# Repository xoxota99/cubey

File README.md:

# Cubey - Rubik's Cube Solving Robot

Cubey is a Raspberry Pi-based Rubik's Cube solving robot that uses computer vision to scan a cube, calculates a solution, and manipulates the cube to solve it using stepper motors.

## Features

- Computer vision-based cube scanning with OpenCV
- Efficient solving algorithm using Kociemba's two-phase algorithm
- Precise stepper motor control for cube manipulation
- Web interface for remote operation
- Command-line interface for local operation
- Comprehensive logging and error handling
- Performance optimizations for faster solving

## Project Structure

```
/
├── config/                     # Configuration files
│   ├── config.yaml             # Main configuration
│   └── calibration.yaml        # Camera calibration
│
├── cubey/                      # Main package directory
│   ├── __init__.py             # Package initialization with version
│   ├── cli.py                  # Command-line interface
│   ├── exceptions.py           # Custom exceptions
│   │
│   ├── config/                 # Configuration management
│   │   ├── __init__.py
│   │   ├── defaults.py         # Default configuration values
│   │   ├── loader.py           # Configuration loading
│   │   ├── schema.py           # Configuration schema
│   │   └── validation.py       # Configuration validation
│   │
│   ├── hardware/               # Hardware interfaces
│   │   ├── __init__.py
│   │   ├── camera.py           # Camera interface
│   │   ├── motorcontroller.py  # Motor controller
│   │   ├── motors.py           # Interactive motor control
│   │   └── calibration.py      # Hardware calibration
│   │
│   ├── solver/                 # Cube solving algorithms
│   │   ├── __init__.py
│   │   ├── kociemba_solver.py  # Kociemba solver
│   │   ├── scanner.py          # Cube state scanner
│   │   └── scrambler.py        # Cube scrambler
│   │
│   ├── ui/                     # User interfaces
│   │   ├── __init__.py
│   │   ├── cli_controller.py   # CLI controller
│   │   └── web_controller.py   # Web interface controller
│   │
│   ├── utils/                  # Utility modules
│   │   ├── __init__.py
│   │   ├── error_handler.py    # Error handling
│   │   ├── logger.py           # Logging setup
│   │   └── logging_config.py   # Logging configuration
│   │
│   └── web/                    # Web interface
│       ├── __init__.py
│       ├── app.py              # Flask application
│       ├── camera.py           # Camera streaming
│       ├── frame_event.py      # Frame event handling
│       ├── integration.py      # API integration
│       ├── security.py         # Security utilities
│       └── webstream.py        # Video streaming
│
├── docs/                       # Documentation
│   ├── api.md                  # API documentation
│   ├── configuration.md        # Configuration guide
│   └── development.md          # Development guide
│
├── scripts/                    # Utility scripts
│   ├── install_dependencies.sh # Install system dependencies
│   └── profile_solver.py       # Solver profiling script
│
├── tests/                      # Test suite
│   ├── __init__.py
│   ├── conftest.py             # Test configuration
│   ├── test_solver.py          # Solver tests
│   └── test_scanner.py         # Scanner tests
│
├── setup.py                    # Package setup
├── pyproject.toml              # Project metadata
├── CONTRIBUTING.md             # Contribution guidelines
├── CHANGELOG.md                # Project changelog
└── README.md                   # This file
```

## Installation

### System Requirements

- Raspberry Pi 3 or newer
- Raspberry Pi Camera Module
- Stepper motors and drivers
- Python 3.10 or newer

### Install System Dependencies

```bash
# Run the dependency installation script
sudo ./scripts/install_dependencies.sh
```

### Install Cubey

```bash
# Create and activate a virtual environment
python -m venv venv
source venv/bin/activate  # On Windows: venv\Scripts\activate

# Install from PyPI
pip install cubey

# Or install from source
pip install -e .
```

## Quick Start

### Command Line Interface

```bash
# Solve a cube
cubey solve

# Scramble a cube
cubey scramble

# Calibrate the scanner
cubey calibrate

# Manual control of motors
cubey manual

# Start the web interface
cubey web
```

### Python API

```python
from cubey.hardware.motorcontroller import MotorController
from cubey.solver.scanner import Scanner
from cubey.solver.kociemba_solver import KociembaSolver
from cubey.config.loader import load_config

# Load configuration
config = load_config()

# Initialize components
scanner = Scanner(config)
motors = MotorController(config)
solver = KociembaSolver(config)

# Scan the cube
state = scanner.get_state_string(motors)

# Solve the cube
solution = solver.solve(state)
motors.execute(solution)
```

## Web Interface

Start the web server:

```bash
cubey web --host 0.0.0.0 --port 5000
```

Then open a browser to http://localhost:5000/

## Configuration

Configuration is stored in YAML files in the `config/` directory:

- `config/config.yaml`: Main configuration
- `config/calibration.yaml`: Camera calibration

You can override the configuration by creating a custom config file and specifying it with the `--config` option:

```bash
cubey --config /path/to/custom_config.yaml solve
```

All default configuration values are defined in `cubey/config/defaults.py`.

## Development

See [CONTRIBUTING.md](CONTRIBUTING.md) for development guidelines.

### Setting Up Development Environment

```bash
# Clone the repository
git clone https://github.com/cubey/cubey.git
cd cubey

# Create and activate a virtual environment
python -m venv venv
source venv/bin/activate  # On Windows: venv\Scripts\activate

# Install in development mode
pip install -e ".[dev]"
```

### Running Tests

```bash
pytest
```

## License

This project is licensed under the MIT License - see the [LICENSE](LICENSE) file for details.

## Acknowledgments

- [Herbert Kociemba](http://kociemba.org/cube.htm) for the two-phase algorithm
- [OpenCV](https://opencv.org/) for computer vision capabilities
- All contributors to this project

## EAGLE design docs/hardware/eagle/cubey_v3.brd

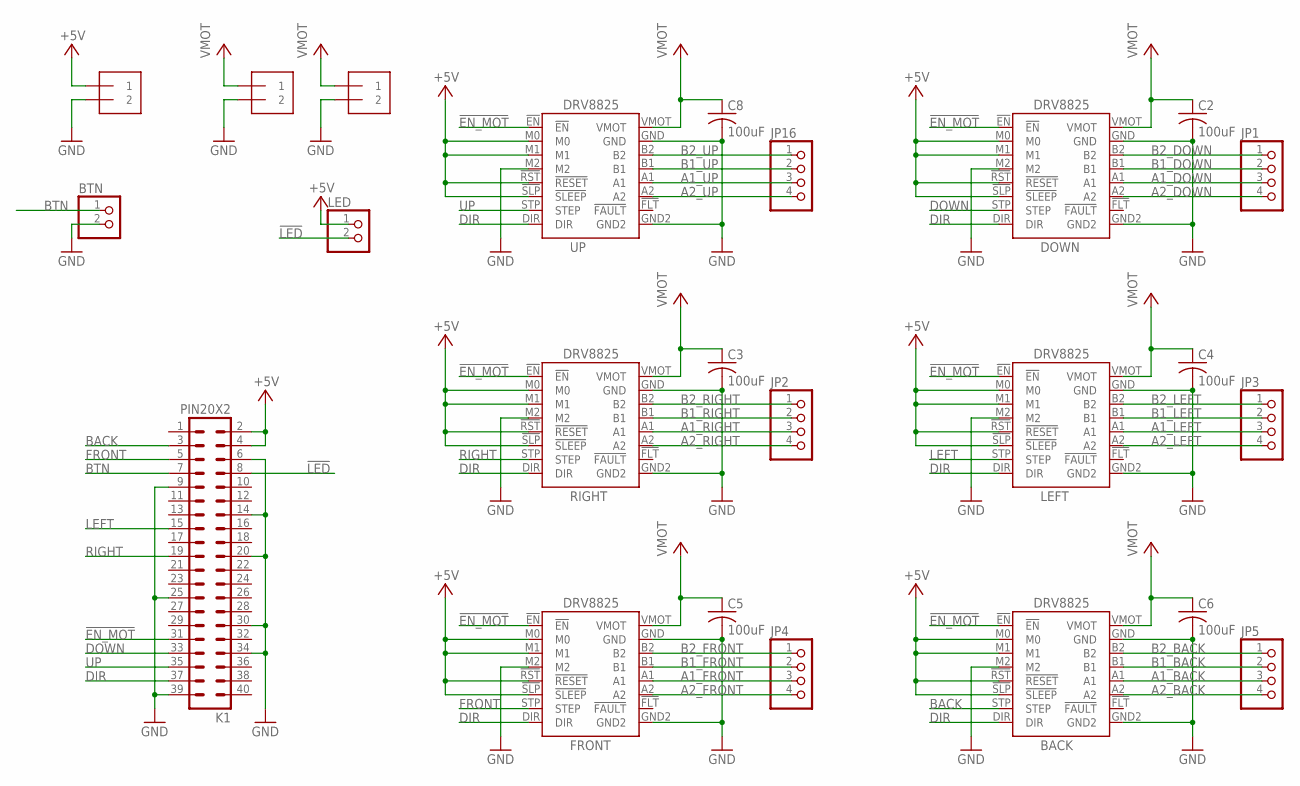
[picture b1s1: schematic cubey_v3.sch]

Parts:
5V_PWR: 1X2-3.5MM
BACK: DRV_8825_SOCKET; DRV_8825_DIP
BTN: PINHD-1X2; 1X02
C2, C3, C4, C5, C6, C8: 100uF; C025-025X050
DOWN: DRV_8825_SOCKET; DRV_8825_DIP
FRONT: DRV_8825_SOCKET; DRV_8825_DIP
JP1, JP2, JP3, JP4, JP5, JP16: PINHD-1X4; 1X04
K1: PIN20X2; PIN_20X2
LED: PINHD-1X2; 1X02
LEFT: DRV_8825_SOCKET; DRV_8825_DIP
MOT_PWR, MOT_PWR1: 1X2-3.5MM
RIGHT: DRV_8825_SOCKET; DRV_8825_DIP
UP: DRV_8825_SOCKET; DRV_8825_DIP

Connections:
!EN_MOT: BACK.!EN, DOWN.!EN, FRONT.!EN, K1.31, LEFT.!EN, RIGHT.!EN, UP.!EN
!LED: K1.8, LED.2
+5V: 5V_PWR.1, BACK.!RST (!RESET), BACK.!SLP (!SLEEP), BACK.M0, BACK.M1, DOWN.!RST (!RESET), DOWN.!SLP (!SLEEP), DOWN.M0, DOWN.M1, FRONT.!RST (!RESET), FRONT.!SLP (!SLEEP), FRONT.M0, FRONT.M1, K1.2, K1.4, LED.1, LEFT.!RST (!RESET), LEFT.!SLP (!SLEEP), LEFT.M0, LEFT.M1, RIGHT.!RST (!RESET), RIGHT.!SLP (!SLEEP), RIGHT.M0, RIGHT.M1, UP.!RST (!RESET), UP.!SLP (!SLEEP), UP.M0, UP.M1
A1_BACK: BACK.A1, JP5.3
A1_DOWN: DOWN.A1, JP1.3
A1_FRONT: FRONT.A1, JP4.3
A1_LEFT: JP3.3, LEFT.A1
A1_RIGHT: JP2.3, RIGHT.A1
A1_UP: JP16.3, UP.A1
A2_BACK: BACK.A2, JP5.4
A2_DOWN: DOWN.A2, JP1.4
A2_FRONT: FRONT.A2, JP4.4
A2_LEFT: JP3.4, LEFT.A2
A2_RIGHT: JP2.4, RIGHT.A2
A2_UP: JP16.4, UP.A2
B1_BACK: BACK.B1, JP5.2
B1_DOWN: DOWN.B1, JP1.2
B1_FRONT: FRONT.B1, JP4.2
B1_LEFT: JP3.2, LEFT.B1
B1_RIGHT: JP2.2, RIGHT.B1
B1_UP: JP16.2, UP.B1
B2_BACK: BACK.B2, JP5.1
B2_DOWN: DOWN.B2, JP1.1
B2_FRONT: FRONT.B2, JP4.1
B2_LEFT: JP3.1, LEFT.B2
B2_RIGHT: JP2.1, RIGHT.B2
B2_UP: JP16.1, UP.B2
BACK: BACK.STP (STEP), K1.3
BTN: BTN.1, K1.7
DIR: BACK.DIR, DOWN.DIR, FRONT.DIR, K1.37, LEFT.DIR, RIGHT.DIR, UP.DIR
DOWN: DOWN.STP (STEP), K1.33
FRONT: FRONT.STP (STEP), K1.5
GND: 5V_PWR.2, BACK.GND, BACK.GND2, BACK.M2, BTN.2, C2.2, C3.2, C4.2, C5.2, C6.2, C8.2, DOWN.GND, DOWN.GND2, DOWN.M2, FRONT.GND, FRONT.GND2, FRONT.M2, K1.6, K1.9, K1.14, K1.20, K1.25, K1.30, K1.34, K1.39, LEFT.GND, LEFT.GND2, LEFT.M2, MOT_PWR.2, MOT_PWR1.2, RIGHT.GND, RIGHT.GND2, RIGHT.M2, UP.GND, UP.GND2, UP.M2
LEFT: K1.15, LEFT.STP (STEP)
RIGHT: K1.19, RIGHT.STP (STEP)
UP: K1.35, UP.STP (STEP)
VCC: BACK.VMOT, C2.1, C3.1, C4.1, C5.1, C6.1, C8.1, DOWN.VMOT, FRONT.VMOT, LEFT.VMOT, MOT_PWR.1, MOT_PWR1.1, RIGHT.VMOT, UP.VMOT

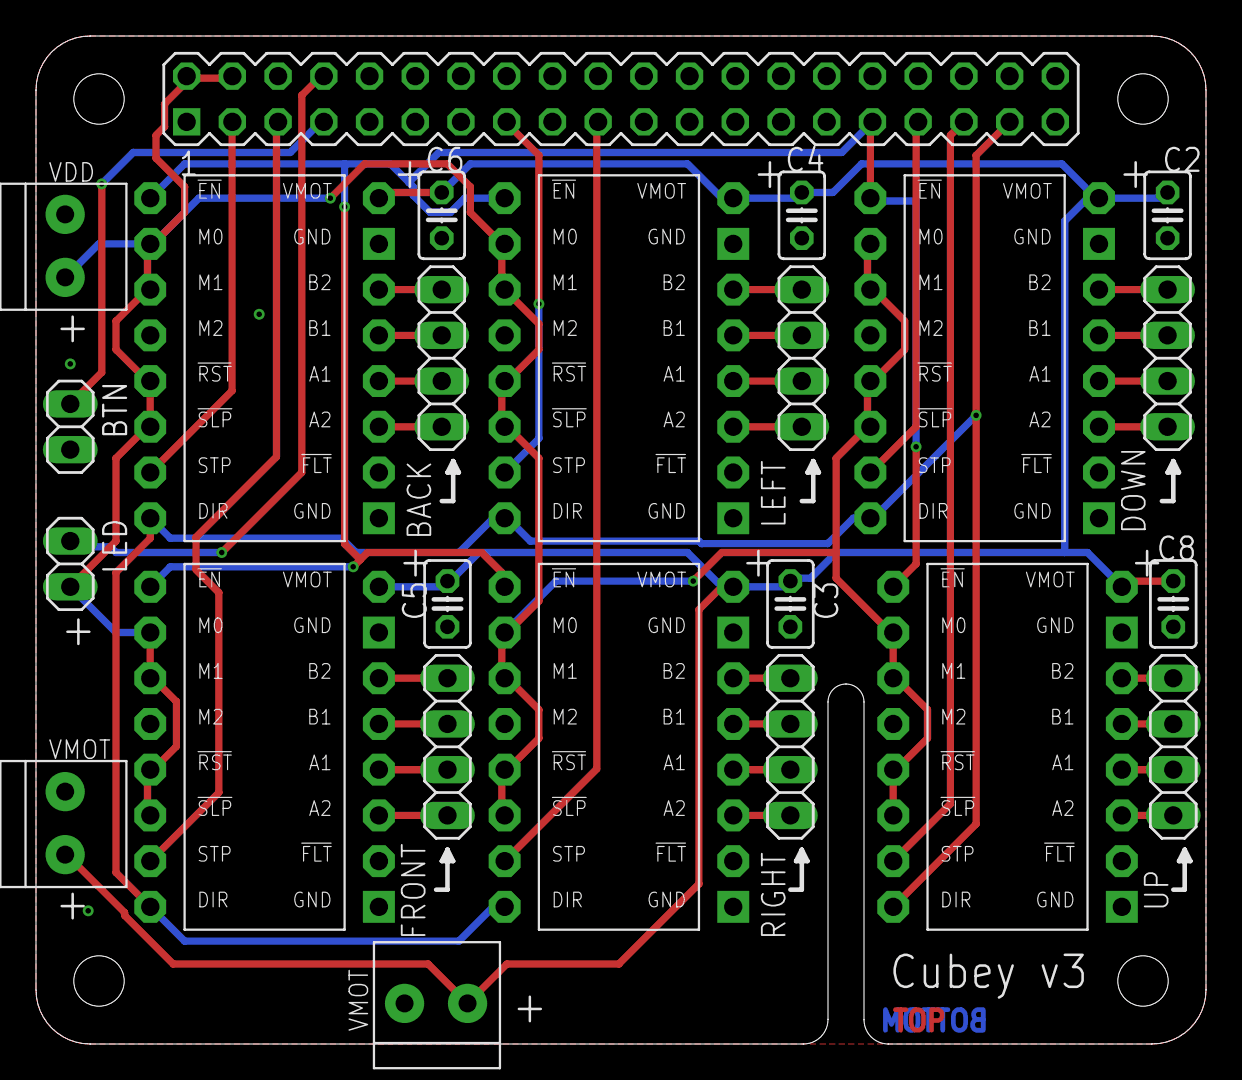
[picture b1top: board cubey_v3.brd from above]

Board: 2 copper layers, 65.0 x 56.0 mm, 24 parts (0 on the bottom side), 37 nets.

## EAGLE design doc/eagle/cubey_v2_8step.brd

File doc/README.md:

# Setting Up your Raspberry Pi
These instructions are for Ubuntu 21.04 or later on Raspberry Pi. Other than service setup, they should be applicable to any debian-based, reasonably recent OS (such as Raspbian, or whatever they're calling it now).

## The Basics
Install Ubuntu Server 21.04 or later: https://ubuntu.com/tutorials/how-to-install-ubuntu-on-your-raspberry-pi#1-overview 

SSH into your new, up-and-running RPi using "ubuntu/ubuntu". Change the password.

Create a new user (here we're creating a user "cubey"):

    sudo adduser cubey
    sudo adduser cubey sudo

(Optional) Enable passwordless login: https://linuxize.com/post/how-to-setup-passwordless-ssh-login/ 

SSH into your RPi as the new user you just created.

**Slow SSH logins?** Disable PAM auth: change `UsePAM` from `yes` to `no` in */etc/ssh/sshd_config*

    UsePAM no

(Optional) change the hostname in */etc/hostname*

(Optional) set the timezone: `sudo dpkg-reconfigure tzdata`

(Optional) install zsh: `sudo apt install zsh`

(Optional) set zsh as your default shell: `chsh -s $(which zsh)`

(Optional) install oh-my-zsh: `sh -c "$(curl -fsSL https://raw.github.com/ohmyzsh/ohmyzsh/master/tools/install.sh)"`

Update to latest of everything: 

    sudo apt update
    sudo apt dist-upgrade

Now would be a good time to reboot the RPi (using `sudo reboot`), and reconnect.

## Install Python (3.9):

    sudo apt install -y build-essential python3-setuptools software-properties-common python3.9 python3.9-venv python3.9-dev python3-pip v4l-utils

Set python 3.9 as the default for python3

    cd /usr/bin

    sudo rm aarch64-linux-gnu-python3-config pdb3 pydoc3 pygettext3 python3 python3-config

    sudo sh -c 'ln -s aarch64-linux-gnu-python3.9-config aarch64-linux-gnu-python3-config && \
    ln -s pdb3.9 pdb3 && \
    ln -s pydoc3.9 pydoc3 && \
    ln -s pygettext3.9 pygettext3 && \
    ln -s python3.9 python3 && \
    ln -s python3.9-config python3-config'

## Install OpenCV
    sudo apt install -y python3-opencv

## Install GPIO support
    sudo apt install python3-rpi.gpio python3-lgpio

## Install PIGPio
    cd
    wget https://github.com/joan2937/pigpio/archive/master.zip
    unzip master.zip
    cd pigpio-master
    make
    sudo make install
    sudo touch /lib/systemd/system/pigpiod.service

Add the following to /lib/systemd/system/pigpiod.service:

    [Unit]
    Description=Daemon required to control GPIO pins via pigpio
    [Service]
    ExecStart=/usr/local/bin/pigpiod
    ExecStop=/bin/systemctl kill -s SIGKILL pigpiod
    Type=forking
    [Install]
    WantedBy=multi-user.target

Setup pigpio to run at startup:

    sudo systemctl enable pigpiod

Reboot again, and reconnect.

## Install cubey
    cd
    git clone https://github.com/xoxota99/cubey.git

## Install cubey dependencies: 
    sudo pip install -r cubey/requirements.txt

This includes:
* The [kociemba](https://pypi.org/project/kociemba/) solver library
* [flask](https://flask.palletsprojects.com/en/2.0.x/) web development framework
* [pillow](https://pillow.readthedocs.io/en/stable/) image library.
* [greenlet](https://greenlet.readthedocs.io/en/latest/) concurrent process library
* Prebuilt [OpenCV libraries](https://pypi.org/project/opencv-python/) for python
* Prebuilt [OpenCV addons](https://pypi.org/project/opencv-contrib-python/) for python

## Enable shutdown button and power LED (Optional)
In */boot/firmware/config.txt*, add the following:

    dtoverlay=gpio-poweroff,gpiopin=14
    dtoverlay=gpio-shutdown,gpio_pin=4,active_low=1

and comment out `enable_uart=1`

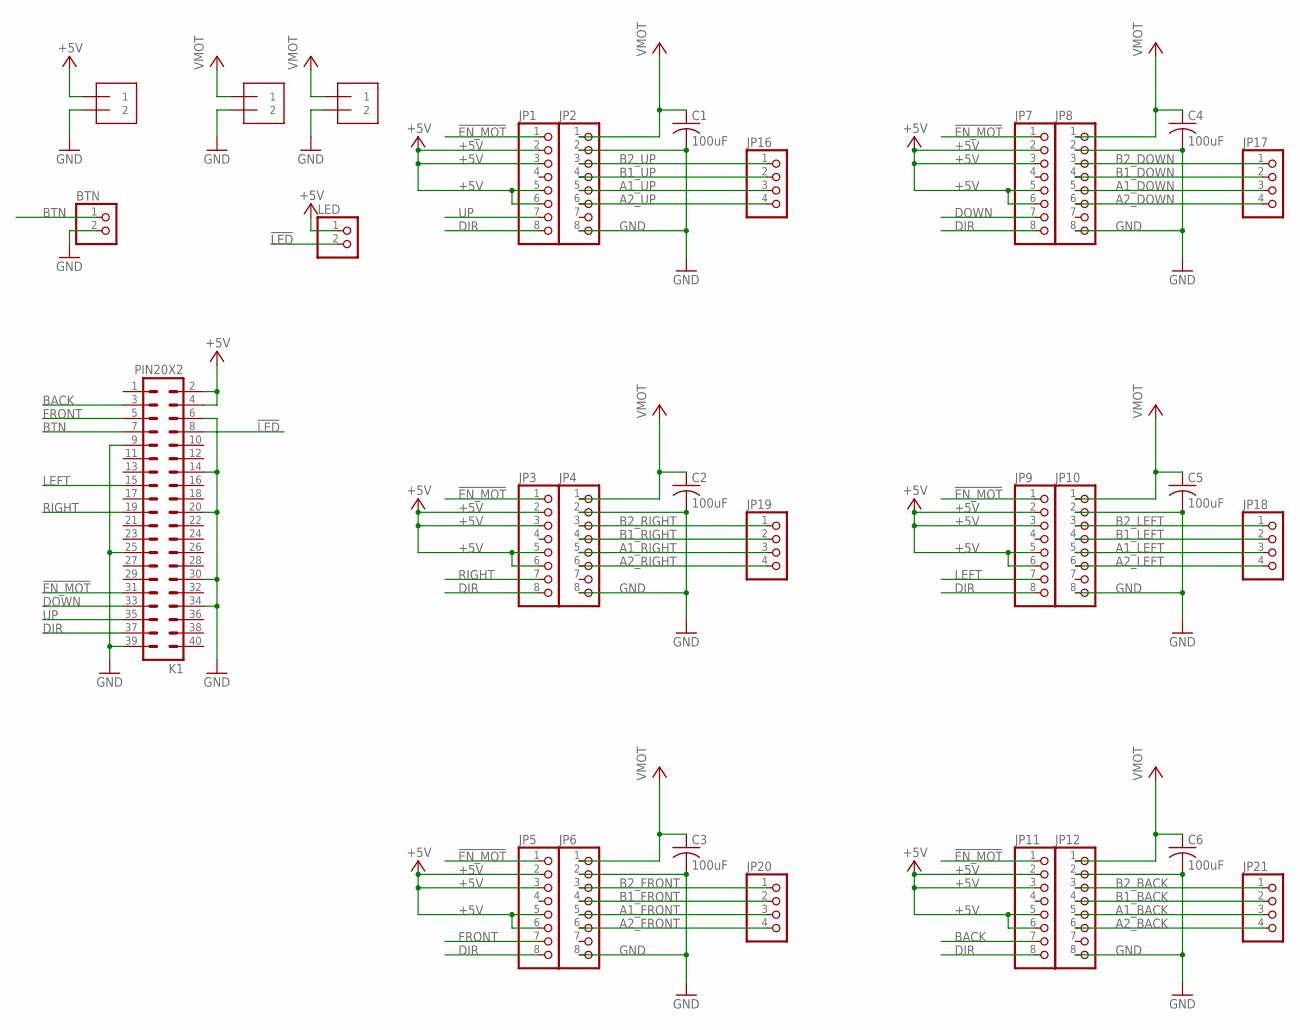
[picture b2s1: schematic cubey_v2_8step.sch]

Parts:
5V_PWR: 1X2-3.5MM
BTN: PINHD-1X2; 1X02
C1, C2, C3, C4, C5, C6: 100uF; C025-025X050
JP1, JP2, JP3, JP4, JP5, JP6, JP7, JP8, JP9, JP10, JP11, JP12: PINHD-1X8; 1X08
JP16, JP17, JP18, JP19, JP20, JP21: PINHD-1X4; 1X04
K1: PIN20X2; PIN_20X2
LED: PINHD-1X2; 1X02
MOT_PWR, MOT_PWR1: 1X2-3.5MM

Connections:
!EN_MOT: JP1.1, JP3.1, JP5.1, JP7.1, JP9.1, JP11.1, K1.31
!LED: K1.8, LED.2
+5V: 5V_PWR.1, JP1.2, JP1.3, JP1.5, JP1.6, JP3.2, JP3.3, JP3.5, JP3.6, JP5.2, JP5.3, JP5.5, JP5.6, JP7.2, JP7.3, JP7.5, JP7.6, JP9.2, JP9.3, JP9.5, JP9.6, JP11.2, JP11.3, JP11.5, JP11.6, K1.2, K1.4, LED.1
A1_BACK: JP12.5, JP21.3
A1_DOWN: JP8.5, JP17.3
A1_FRONT: JP6.5, JP20.3
A1_LEFT: JP10.5, JP18.3
A1_RIGHT: JP4.5, JP19.3
A1_UP: JP2.5, JP16.3
A2_BACK: JP12.6, JP21.4
A2_DOWN: JP8.6, JP17.4
A2_FRONT: JP6.6, JP20.4
A2_LEFT: JP10.6, JP18.4
A2_RIGHT: JP4.6, JP19.4
A2_UP: JP2.6, JP16.4
B1_BACK: JP12.4, JP21.2
B1_DOWN: JP8.4, JP17.2
B1_FRONT: JP6.4, JP20.2
B1_LEFT: JP10.4, JP18.2
B1_RIGHT: JP4.4, JP19.2
B1_UP: JP2.4, JP16.2
B2_BACK: JP12.3, JP21.1
B2_DOWN: JP8.3, JP17.1
B2_FRONT: JP6.3, JP20.1
B2_LEFT: JP10.3, JP18.1
B2_RIGHT: JP4.3, JP19.1
B2_UP: JP2.3, JP16.1
BACK: JP11.7, K1.3
BTN: BTN.1, K1.7
DIR: JP1.8, JP3.8, JP5.8, JP7.8, JP9.8, JP11.8, K1.37
DOWN: JP7.7, K1.33
FRONT: JP5.7, K1.5
GND: 5V_PWR.2, BTN.2, C1.2, C2.2, C3.2, C4.2, C5.2, C6.2, JP2.2, JP2.8, JP4.2, JP4.8, JP6.2, JP6.8, JP8.2, JP8.8, JP10.2, JP10.8, JP12.2, JP12.8, K1.6, K1.9, K1.14, K1.20, K1.25, K1.30, K1.34, K1.39, MOT_PWR.2, MOT_PWR1.2
LEFT: JP9.7, K1.15
RIGHT: JP3.7, K1.19
UP: JP1.7, K1.35
VCC: C1.1, C2.1, C3.1, C4.1, C5.1, C6.1, JP2.1, JP4.1, JP6.1, JP8.1, JP10.1, JP12.1, MOT_PWR.1, MOT_PWR1.1

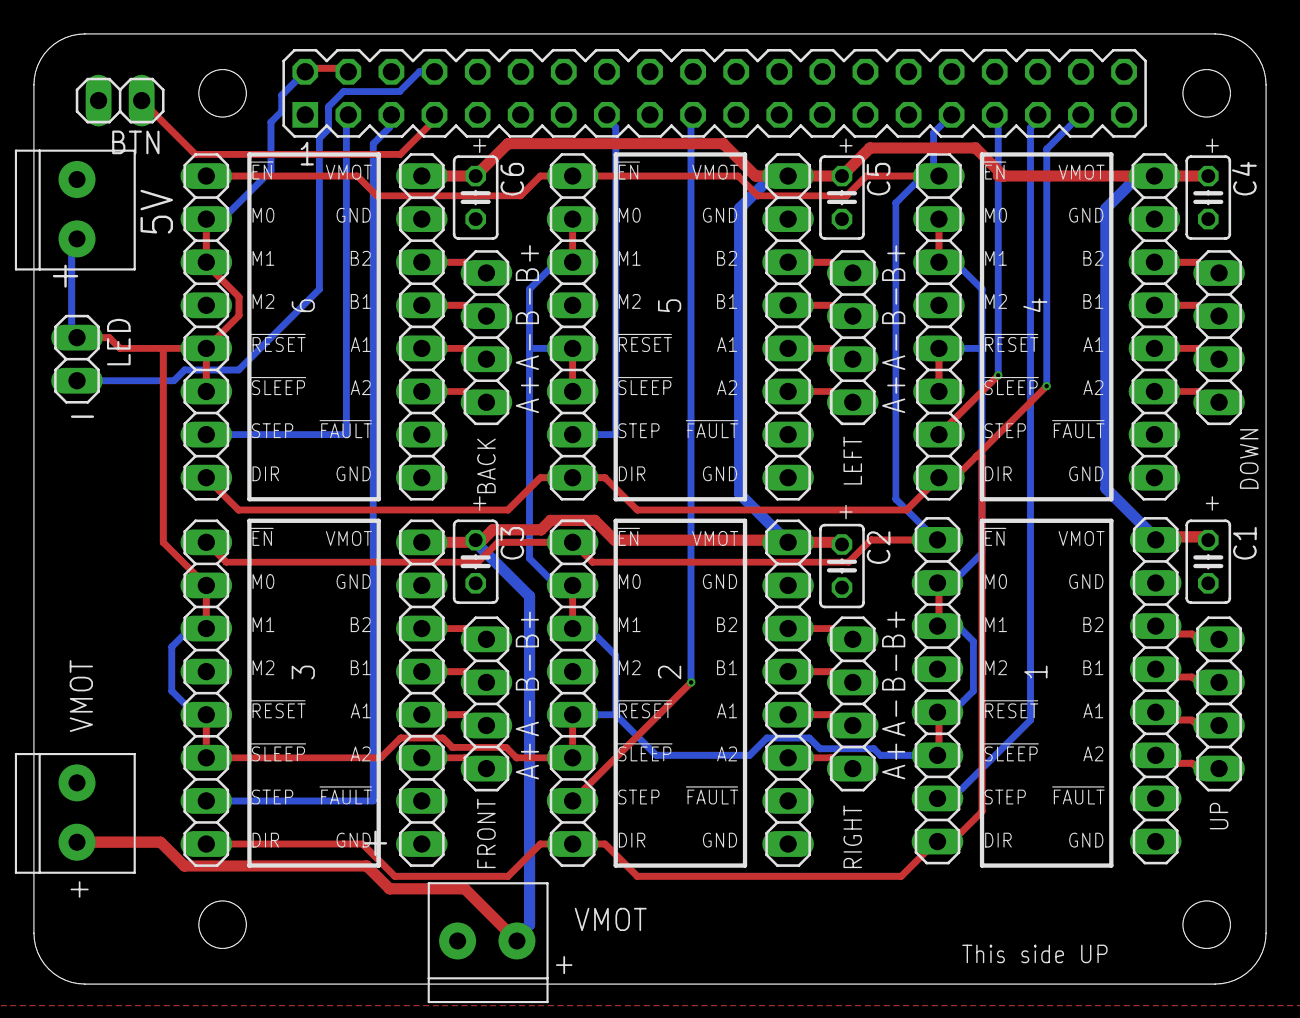
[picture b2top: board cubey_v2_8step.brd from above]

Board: 2 copper layers, 72.6 x 56.0 mm, 30 parts (0 on the bottom side), 37 nets.

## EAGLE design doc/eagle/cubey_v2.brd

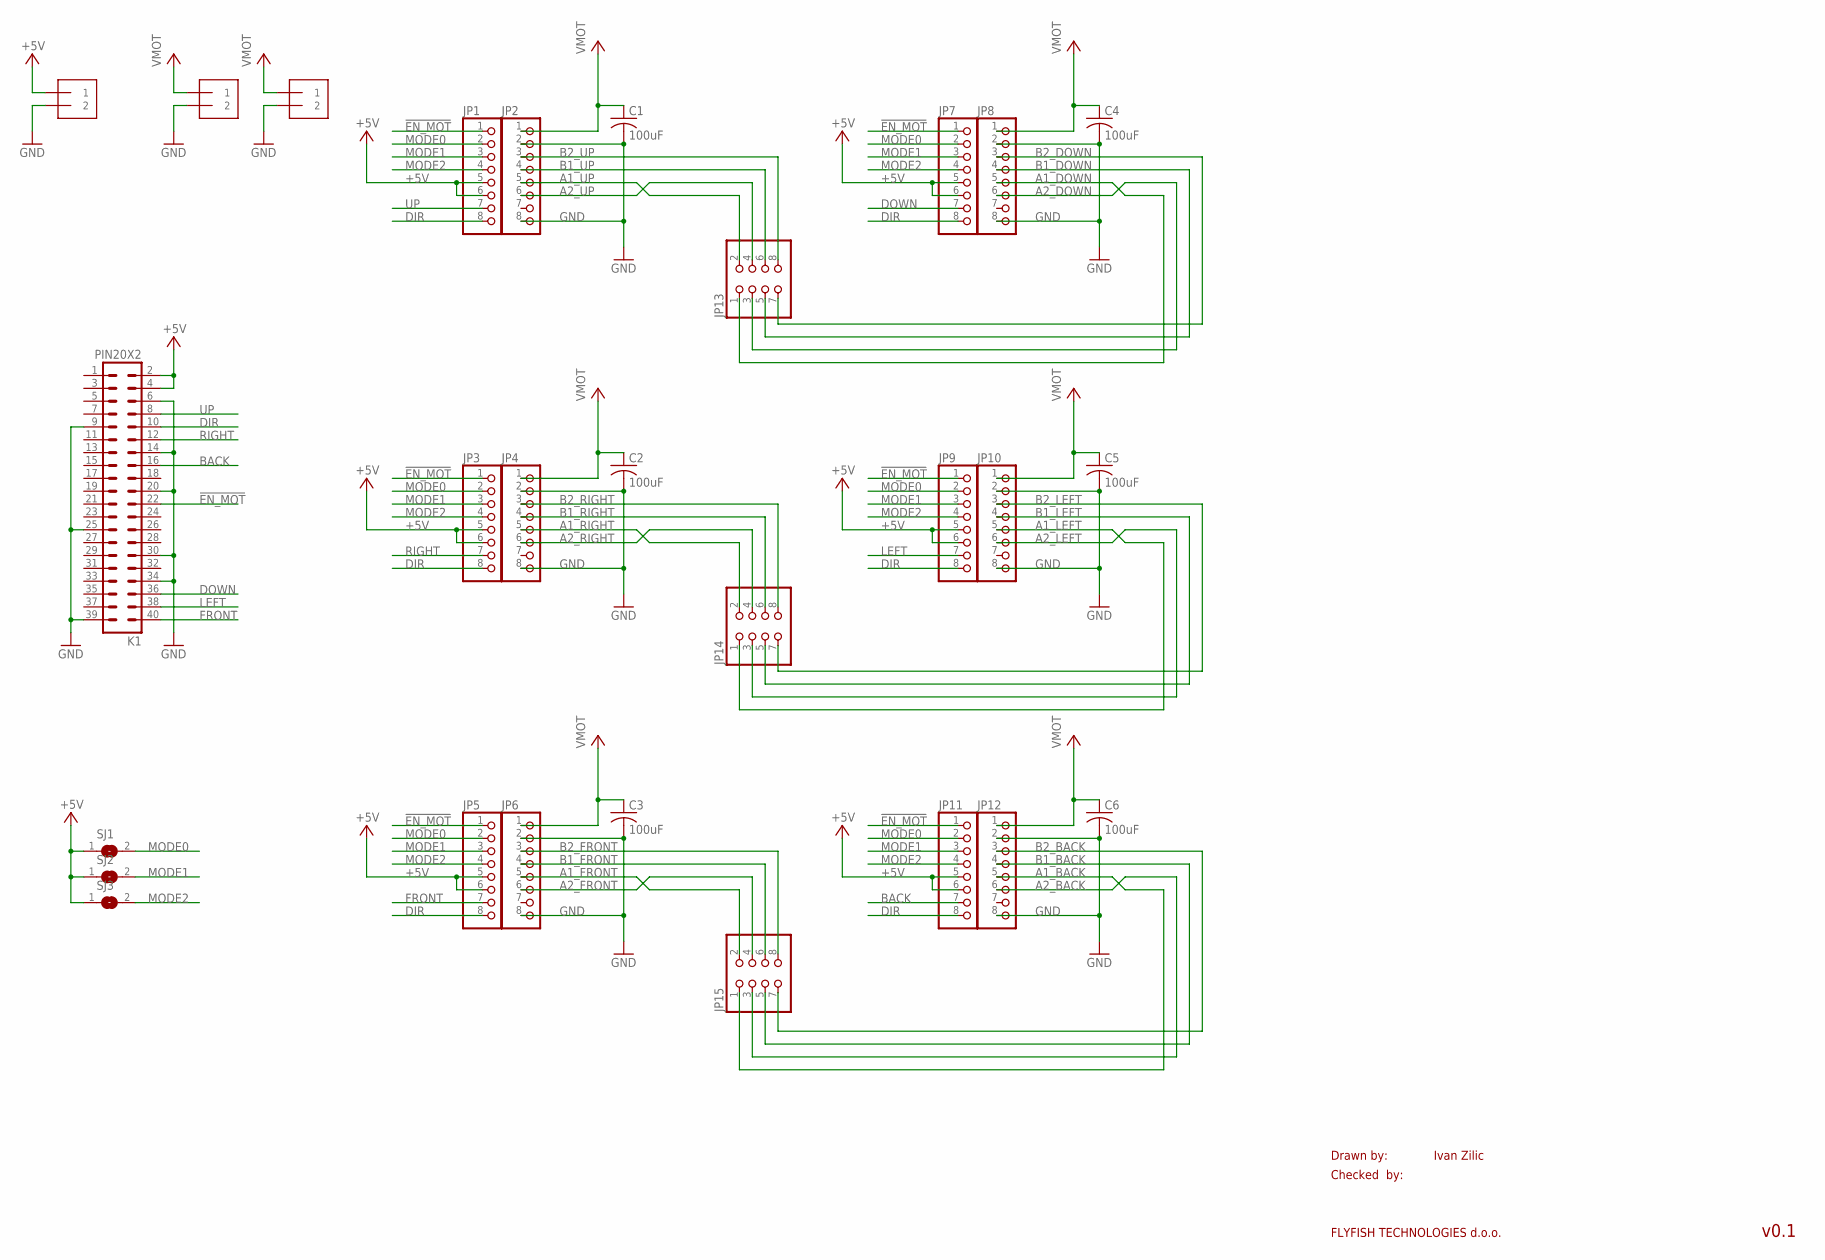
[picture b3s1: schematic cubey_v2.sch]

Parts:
5V_PWR: 1X2-3.5MM
C1, C2, C3, C4, C5, C6: 100uF; C025-025X050
JP1, JP2, JP3, JP4, JP5, JP6, JP7, JP8, JP9, JP10, JP11, JP12: PINHD-1X8; 1X08
JP13, JP14, JP15: PINHD-2X4; 2X04
K1: PIN20X2; PIN_20X2
MOT_PWR, MOT_PWR1: 1X2-3.5MM
SJ1, SJ2, SJ3: SJ

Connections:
!EN_MOT: JP1.1, JP3.1, JP5.1, JP7.1, JP9.1, JP11.1, K1.22
+5V: 5V_PWR.1, JP1.5, JP1.6, JP3.5, JP3.6, JP5.5, JP5.6, JP7.5, JP7.6, JP9.5, JP9.6, JP11.5, JP11.6, K1.2, K1.4, SJ1.1, SJ2.1, SJ3.1
A1_BACK: JP12.5, JP15.1
A1_DOWN: JP8.5, JP13.1
A1_FRONT: JP6.5, JP15.2
A1_LEFT: JP10.5, JP14.1
A1_RIGHT: JP4.5, JP14.2
A1_UP: JP2.5, JP13.2
A2_BACK: JP12.6, JP15.3
A2_DOWN: JP8.6, JP13.3
A2_FRONT: JP6.6, JP15.4
A2_LEFT: JP10.6, JP14.3
A2_RIGHT: JP4.6, JP14.4
A2_UP: JP2.6, JP13.4
B1_BACK: JP12.4, JP15.5
B1_DOWN: JP8.4, JP13.5
B1_FRONT: JP6.4, JP15.6
B1_LEFT: JP10.4, JP14.5
B1_RIGHT: JP4.4, JP14.6
B1_UP: JP2.4, JP13.6
B2_BACK: JP12.3, JP15.7
B2_DOWN: JP8.3, JP13.7
B2_FRONT: JP6.3, JP15.8
B2_LEFT: JP10.3, JP14.7
B2_RIGHT: JP4.3, JP14.8
B2_UP: JP2.3, JP13.8
BACK: JP11.7, K1.16
DIR: JP1.8, JP3.8, JP5.8, JP7.8, JP9.8, JP11.8, K1.10
DOWN: JP7.7, K1.36
FRONT: JP5.7, K1.40
GND: 5V_PWR.2, C1.2, C2.2, C3.2, C4.2, C5.2, C6.2, JP2.2, JP2.8, JP4.2, JP4.8, JP6.2, JP6.8, JP8.2, JP8.8, JP10.2, JP10.8, JP12.2, JP12.8, K1.6, K1.9, K1.14, K1.20, K1.25, K1.30, K1.34, K1.39, MOT_PWR.2, MOT_PWR1.2
LEFT: JP9.7, K1.38
MODE0: JP1.2, JP3.2, JP5.2, JP7.2, JP9.2, JP11.2, SJ1.2
MODE1: JP1.3, JP3.3, JP5.3, JP7.3, JP9.3, JP11.3, SJ2.2
MODE2: JP1.4, JP3.4, JP5.4, JP7.4, JP9.4, JP11.4, SJ3.2
RIGHT: JP3.7, K1.12
UP: JP1.7, K1.8
VCC: C1.1, C2.1, C3.1, C4.1, C5.1, C6.1, JP2.1, JP4.1, JP6.1, JP8.1, JP10.1, JP12.1, MOT_PWR.1, MOT_PWR1.1

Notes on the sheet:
Drawn by:
Checked by:
FLYFISH TECHNOLOGIES d.o.o.
Ivan Zilic
v0.1

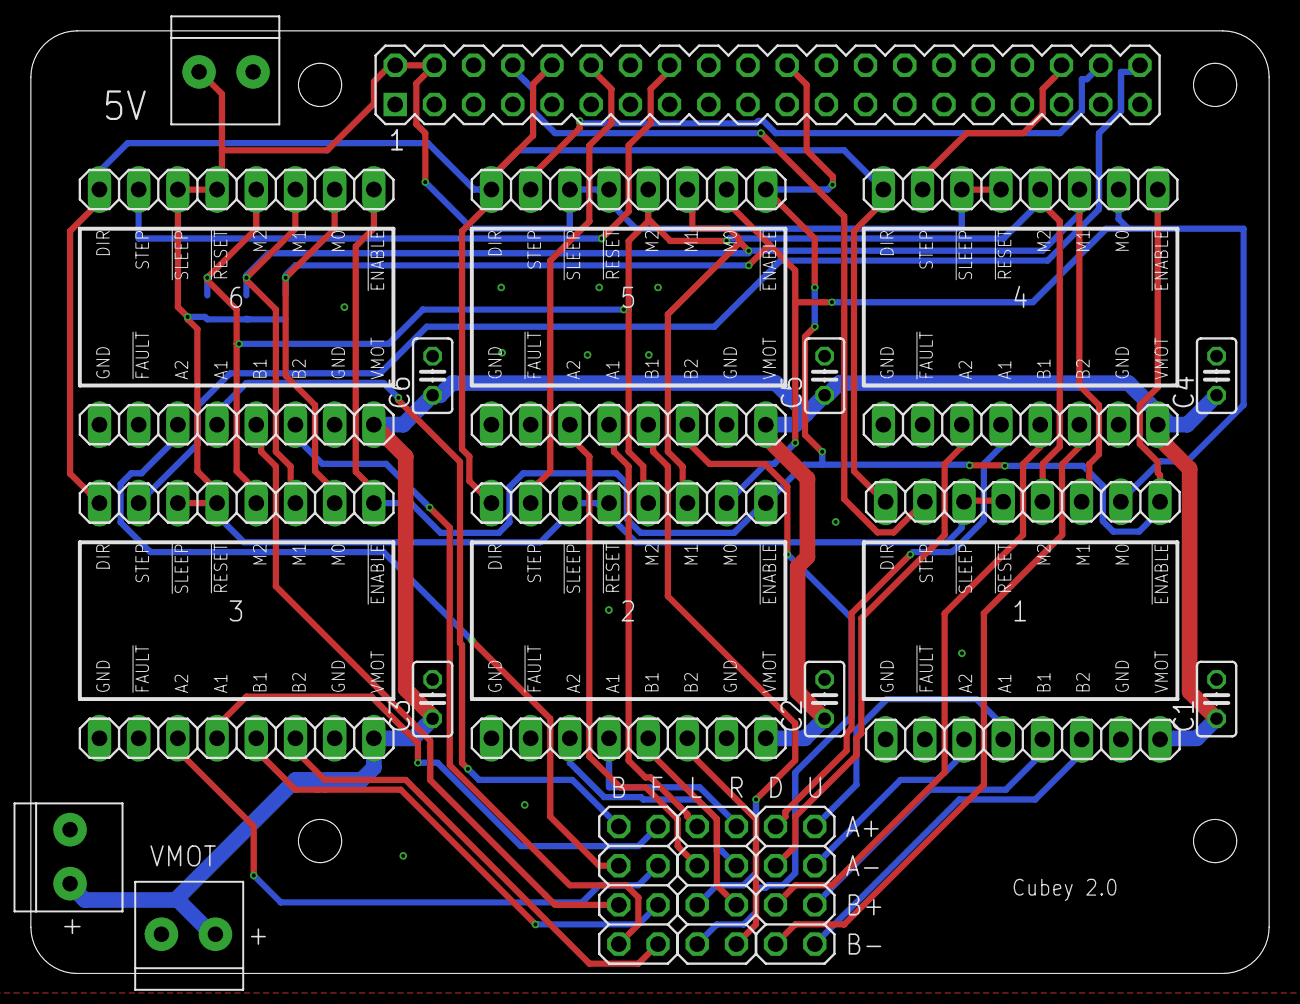
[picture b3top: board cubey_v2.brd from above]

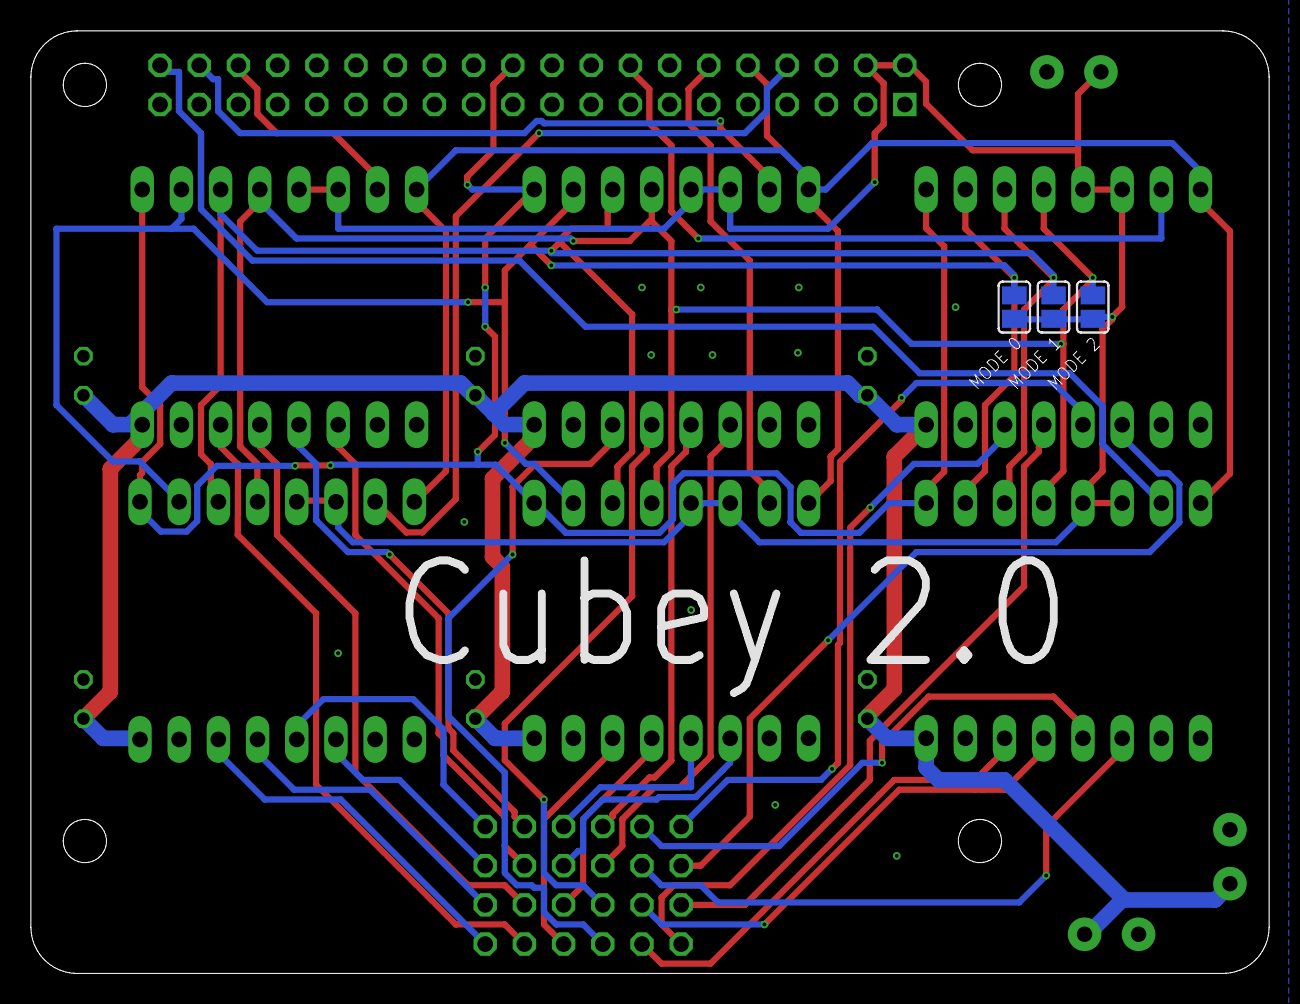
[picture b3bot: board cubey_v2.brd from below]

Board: 2 copper layers, 80.2 x 61.1 mm, 28 parts (3 on the bottom side), 38 nets.

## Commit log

2018-10-15 Initial Commit. Still missing OpenCV / state estimation.
2018-10-16 Added Case design for Raspberry PI and power supply, dimensionanl drawing for camera
2018-10-16 Updated Cube State estimator. Still missing final pixel sampling coordinates in cam.py.
2018-10-16 remove the "tongue" from the board layout. SVG logo.
2018-10-16 Sample image from front-right camera (60 deg. FOV)
2018-10-19 Added FreeCAD models
2018-10-19 Refactor webstream
2018-10-19 refactor cubey and camera. Add timing instrumentation
2018-10-19 rename 'cubey.py' to 'app.py'
2018-10-19 update webstream app to support dual cameras
2018-10-19 read config from yaml
2018-10-20 Added STL file for the camera mount.
2018-10-20 deleted unnecessary imges, added basic BOM
2018-10-21 Updated BOM
2018-10-21 Added Solder jumpers for M0, M1 and M2
2018-10-21 Added random scramble function
2018-10-21 Simplifying Stepper driver.
2018-10-21 Added test scripts for stepper functinos.
2018-10-21 Updates to delay tables.
2018-10-22 New version of DRV8825 carrier, to get around some GPIO issues.
2018-10-22 Create a Trim utility script, for moving motors at specific steps.
2018-10-22 Fixed Scramble function, added Cubey v2 pcb pinmap.
2018-10-22 Minor bugfixes and tweaks
2018-10-22 step_pigpio is now an interactive command-line cube mover.
2018-10-23 Trivial code cleanup
2018-10-24 Rename signals in Cubey PCB design. Finalized V2 with ENABLE pin.
2018-10-24 Updated BOM with Dubey PCB v2 link
2018-10-24 Added pinouts / wiring diagrams
2018-10-24 Moved scanning logic to "scanner" module.
2018-10-24 Celanup dead code, disable steppers when not in use.
2018-10-24 Fixed color sample coords, added real devices.
2018-10-24 minor fix.
2018-10-24 Disable motors when not in use (if the disable pin is defined).
2018-10-24 Fixed defaultSampleCoords.
2018-12-01 Add .DS_Store to .gitignore
2018-12-01 Update Case Plans SVG
2018-12-01 Restructure / pythonify. Added init.py
2018-12-01 Updated STL files
2018-12-01 Removed obsolete docs.
2018-12-01 Added links to Fusion 360 CAD files, updated Cubey PCB EAGLE files.
2018-12-02 Fixed config for cubey PCB
2018-12-02 Moved scramble to utility script.
2018-12-02 Fixed imports
2018-12-02 Moved Calibration to a utility script
2018-12-02 Pythonifying package structure. Sort of.
2018-12-07 refactor config, move generic code into classes.
2018-12-07 comments
2018-12-07 Mock RPi.GPIO
2018-12-18 Added a link to the OSHPark project.
2018-12-18 Cleanup dead code
2018-12-18 Fixed param modeling
2018-12-18 Added interactive mode.
2018-12-18 Objectify stepper motor control
2018-12-18 move config
2018-12-18 Objectify MotorController
2018-12-18 refactor / cleanup
2019-04-12 updated PCB
2020-02-11 fixing sonarcloud code smells
2020-02-11 fixing sonarcloud bugs
2020-02-11 sonarcloud fixes
2020-02-11 Add sonarcloud metrics to readme.md
2020-02-11 Adding basic unit testing
2020-02-11 reorganization of sonarcloud tags
2020-04-03 Cleanup
2021-09-06 Fix config bug (using "B" and "T" instead of "D" and "U")
2021-09-06 General improvements to readability (comments and variable names)
2021-09-06 General improvements to legibility (comments)
2021-09-06 FIX: short-circuit return in get_faces
2021-09-06 Remove RPi.GPIO, in favor of pigpio
2021-09-06 Code smells (making sonarCloud happy)
2021-09-07 calibration scan efficiency improvement
2021-09-07 fix missing edgelets in scanner
2021-09-07 Add a manual calibration test utility
2021-09-07 Add collision-detect to manual calibration tester.
2021-09-07 ignore VSCode workspace files.
2021-09-08 more calibration tests
2021-09-08 switch to use HSV instead of RGB for color detection
2021-09-08 fix yaml loading, per https://msg.pyyaml.org/load
2021-09-08 making sonarcloud happy
2021-09-08 sonarcloud exclude tests
2021-09-08 fix kociemba tester for python3, add profiling.
2021-09-08 refactor / decomplexify for sonarCloud
2021-09-08 refactor / decomplexify
2021-09-08 improved image generation
2021-09-08 bug fixes for __main__
2021-09-08 remove commented code
2021-09-08 enable SonarCloud on build.
2021-09-08 sonarcloud config
2021-09-09 Update v3 board layout, with cutout for RPi camera, remove of v2 designs
2021-09-09 rename / restructure files
2021-09-09 rename app.py to cubey.py
2021-09-09 clean up web streamer
2021-09-09 fix special HSV cases (for red)
2021-09-09 remove OYBRWG (color) values, in favor of FURBDL values.
2021-09-09 fix typos in calibration steps
2021-09-09 reduce complexity in calibration
2021-09-09 reducing complexity of collision detect
2021-09-09 FIX calibrate
2021-09-09 updated board layout
2021-09-10 Getting git workflows working for sonarcloud
2021-09-11 remove Sonar project config.
2021-09-11 fix github/sonarcloud integration
2021-09-11 removing CI analysis, in favor of automatic analysis.
2021-09-12 fix scramble moves min/max range
2021-09-12 replace print() with logging
2021-09-14 misc bug fixes.
2021-09-14 naming convnentionns
2021-09-17 fix KeyError
2021-09-17 fixes to shutdown script, for pigpio
2021-09-17 shebang!
2021-09-18 fixes to power net class, adding room for capacitors
2021-09-19 remove wrapper for C kociemba, in favor of python package
2021-09-19 replace logging.warn with logging.warning
2021-09-19 swap CW and CCW
2021-09-19 efficiency improvement when writing image output file
2021-09-19 color bracket config tester
2021-09-19 write click coordinates to console.log, to help with configuration
2021-09-19 Slightly improved KeyboardInterrupt, to prevent camera locking up.
2021-09-19 fixes to config
2021-09-20 Remove shutdown script, create requirements text, added build book.
2021-09-21 Adding a basic "build book" for setting up Cubey.
2021-09-21 Adding comments, general readability improvements
2025-05-30 Fix path resolution issues in Scanner class for better cross-directory compatibility
2025-05-30 Improve error handling in Scanner's get_state_string method by returning None instead of empty string
2025-05-30 Add error handling in cubey.py for cases where scanner returns None
2025-05-30 Add direction parameter to rot_180 method for consistency with rot_90
2025-05-30 Add exception handling in MotorController._initialize to prevent resource leaks
2025-05-30 Fix calibration logic error by resetting min/max HSV values for each color
2025-05-30 Fix argument parsing issue by initializing return value before conditional
2025-05-30 Improve warmup_frames method to handle frame grab failures and add synchronization
2025-05-30 Fix HSV color space handling for red to properly handle edge cases
2025-05-30 Fix configuration file path resolution using absolute paths
2025-05-30 Standardize logging approach with centralized logger module
2025-05-30 Add validation and error handling for motor execution with cube notation
2025-05-30 Add proper camera resource management with __del__ and close methods
2025-05-30 Add comprehensive unit tests for Scanner and MotorController classes
2025-05-30 Add detailed docstrings and refactor global variables into class attributes
2025-05-30 Add configuration validation to prevent runtime errors
2025-05-30 Add comprehensive requirements.txt with version pinning
2025-05-30 Add enhanced command-line interface with argparse
2025-05-30 Add type hints to scanner.py for better code documentation and static type checking
2025-05-30 Add type hints to camera.py for improved code quality and static analysis
2025-05-30 Improve web interface with API integration and responsive UI
2025-05-30 Restructure project to follow Python package best practices
2025-05-30 Add CI/CD configuration with tox and GitHub Actions
2025-05-30 Add contribution guidelines and changelog
2025-05-30 Add comprehensive documentation with MkDocs
2025-05-30 Add custom exceptions and global error handling
2025-05-30 Add utility scripts for installation and service setup
2025-05-30 Improve README with comprehensive installation and usage instructions
2025-05-30 Add pre-commit hooks for code quality enforcement
2025-05-30 Add enhanced configuration management with environment variable support
2025-05-30 Add enhanced logging with rotating file handlers
2025-05-30 Add web security features with CSRF protection and input sanitization
2025-05-30 Migrate remaining files from src to new structure
2025-05-30 Add comprehensive tests for camera and web interface
2025-05-30 Update CLI to use new package structure and add improved error handling
2025-05-30 Remove redundant src directory in favor of new package structure
2025-05-30 Update changelog with latest improvements
2025-05-30 Migrate hardware documentation from doc to docs/hardware
2025-05-30 Update mkdocs.yml to include hardware documentation
2025-05-30 Remove redundant doc directory in favor of docs
2025-05-30 Update changelog to reflect doc directory merge
2025-05-30 Update project to use Python 3.10+ instead of 3.7+
2025-05-30 Reorganize project into more consistent module structure
2025-05-30 Update README to reflect new module organization
2025-05-30 Update changelog to reflect module reorganization
2025-05-30 Implement dedicated configuration module
2025-05-30 Update changelog to reflect configuration module addition
2025-06-02 Move configuration files from cubey/data/ to top-level config/ directory
2025-06-02 Adding test cases and expected results for Kociemba
2025-06-02 Standardize module organization by consolidating related functionality
2025-06-02 Clean up codebase by removing deprecated files and directories
2025-06-02 Add type annotations and improve code quality
2025-06-02 Fix unterminated quotes.
2025-06-02 Remove unused imports to improve code quality
2025-06-02 Fix incorrect import of removed core.cube_solver module
2025-06-02 ignore temp_venv
2025-06-02 Fix import issues and add missing Scrambler class
2025-06-02 Conditional / Mock import of RPI.GPIO
2025-06-02 Fix remaining import issues and add type annotations to web modules
2025-06-02 new: Implement semantic versioning strategy
2025-06-02 Fix motorcontroller
2025-06-02 Fix MotorController config
2025-06-02 Update README to reflect new module organization and folder structure
2025-06-02 fix flake8 warnings
2025-06-02 Consolidating config and config validation
2025-06-02 Standardized config naming ('motor' to 'motors')
2025-06-02 Centralized configuration defaults in config/defaults.py and updated all modules to directly access these values without redundant fallback mechanisms. This change improves maintainability by establi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
2025-06-02 Update README to reflect current project structure and configuration approach
2025-06-02 Clean up web module with proper type annotations and improved documentation
2025-06-02 Improve error handling for configuration issues with more robust validation and clearer error messages
2025-06-02 Updated user documentation

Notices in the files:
README.md:
License: MIT
